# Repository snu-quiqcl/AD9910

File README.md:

# AD9910 Control RTL Code and Python Program
## Overview
## AD9910 Mode

The AD9910 is a Direct Digital Synthesizer (DDS) with four modes of operation: single tone mode, RAM modulation mode, digital ramp modulation mode, and parallel data port modulation mode. In our application, we use only the RAM mode and single tone mode. The source of the three parameters varies in each mode. The sources of these parameters for each mode are listed in the table below.

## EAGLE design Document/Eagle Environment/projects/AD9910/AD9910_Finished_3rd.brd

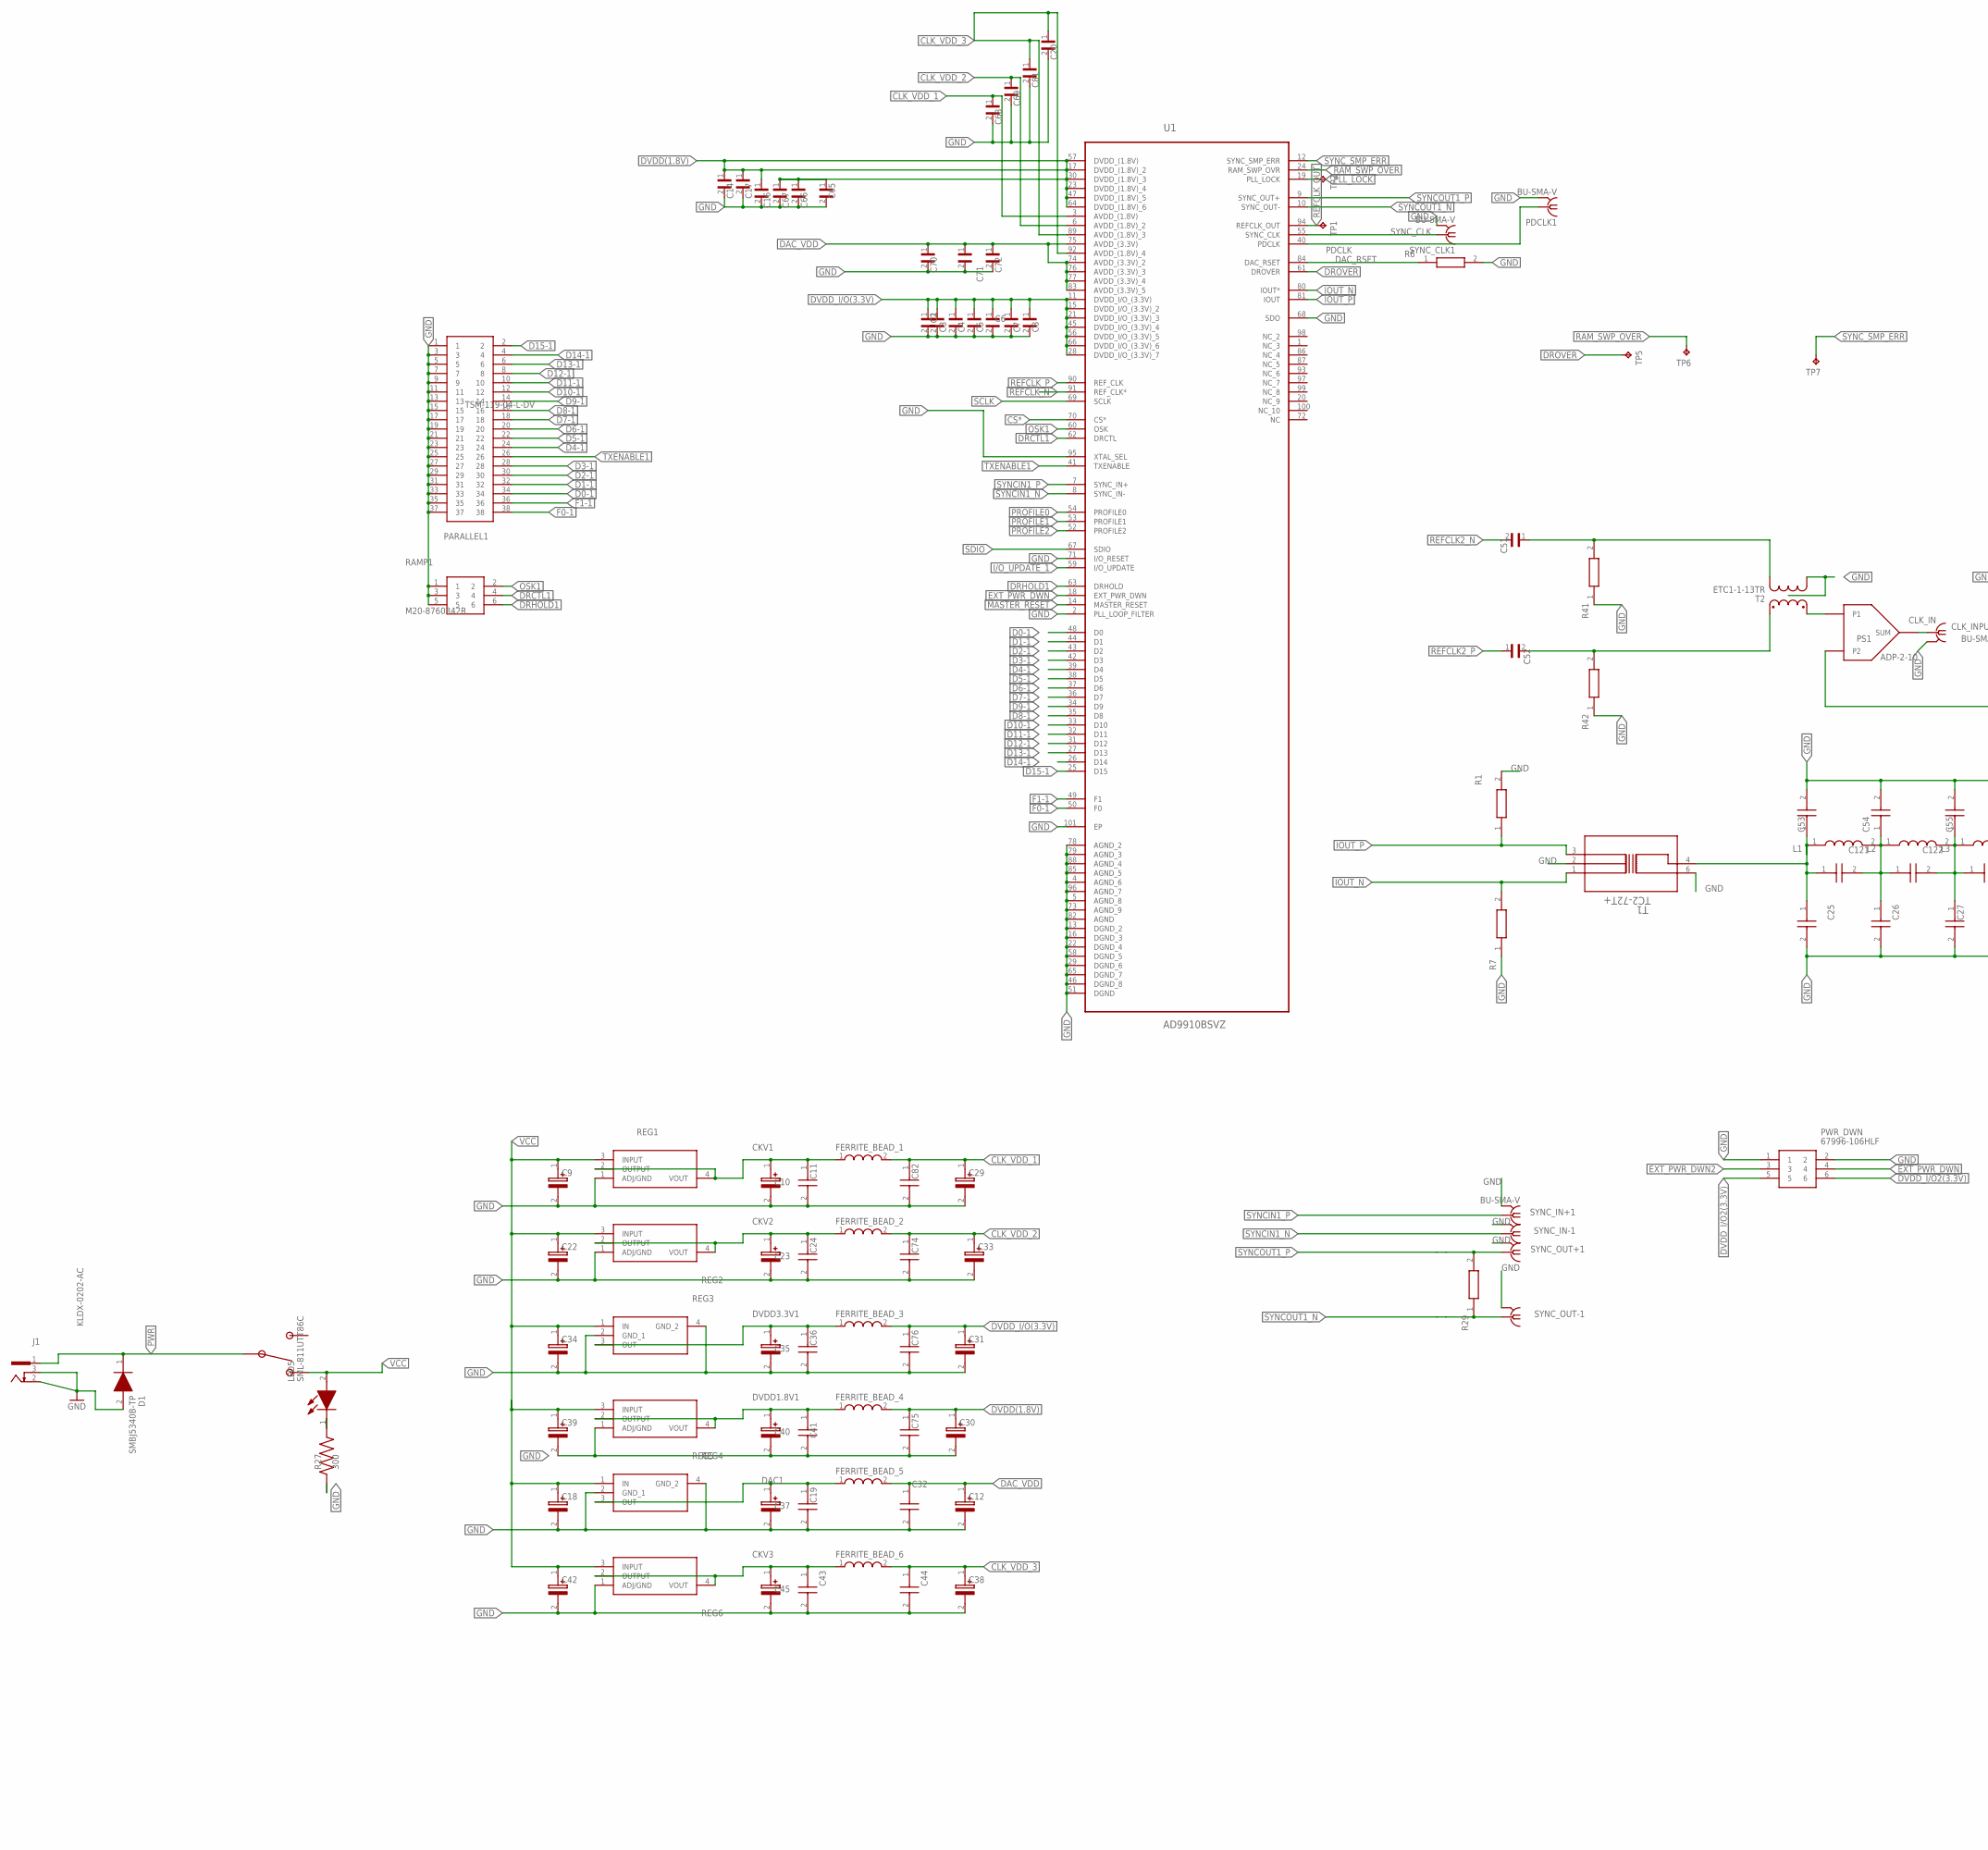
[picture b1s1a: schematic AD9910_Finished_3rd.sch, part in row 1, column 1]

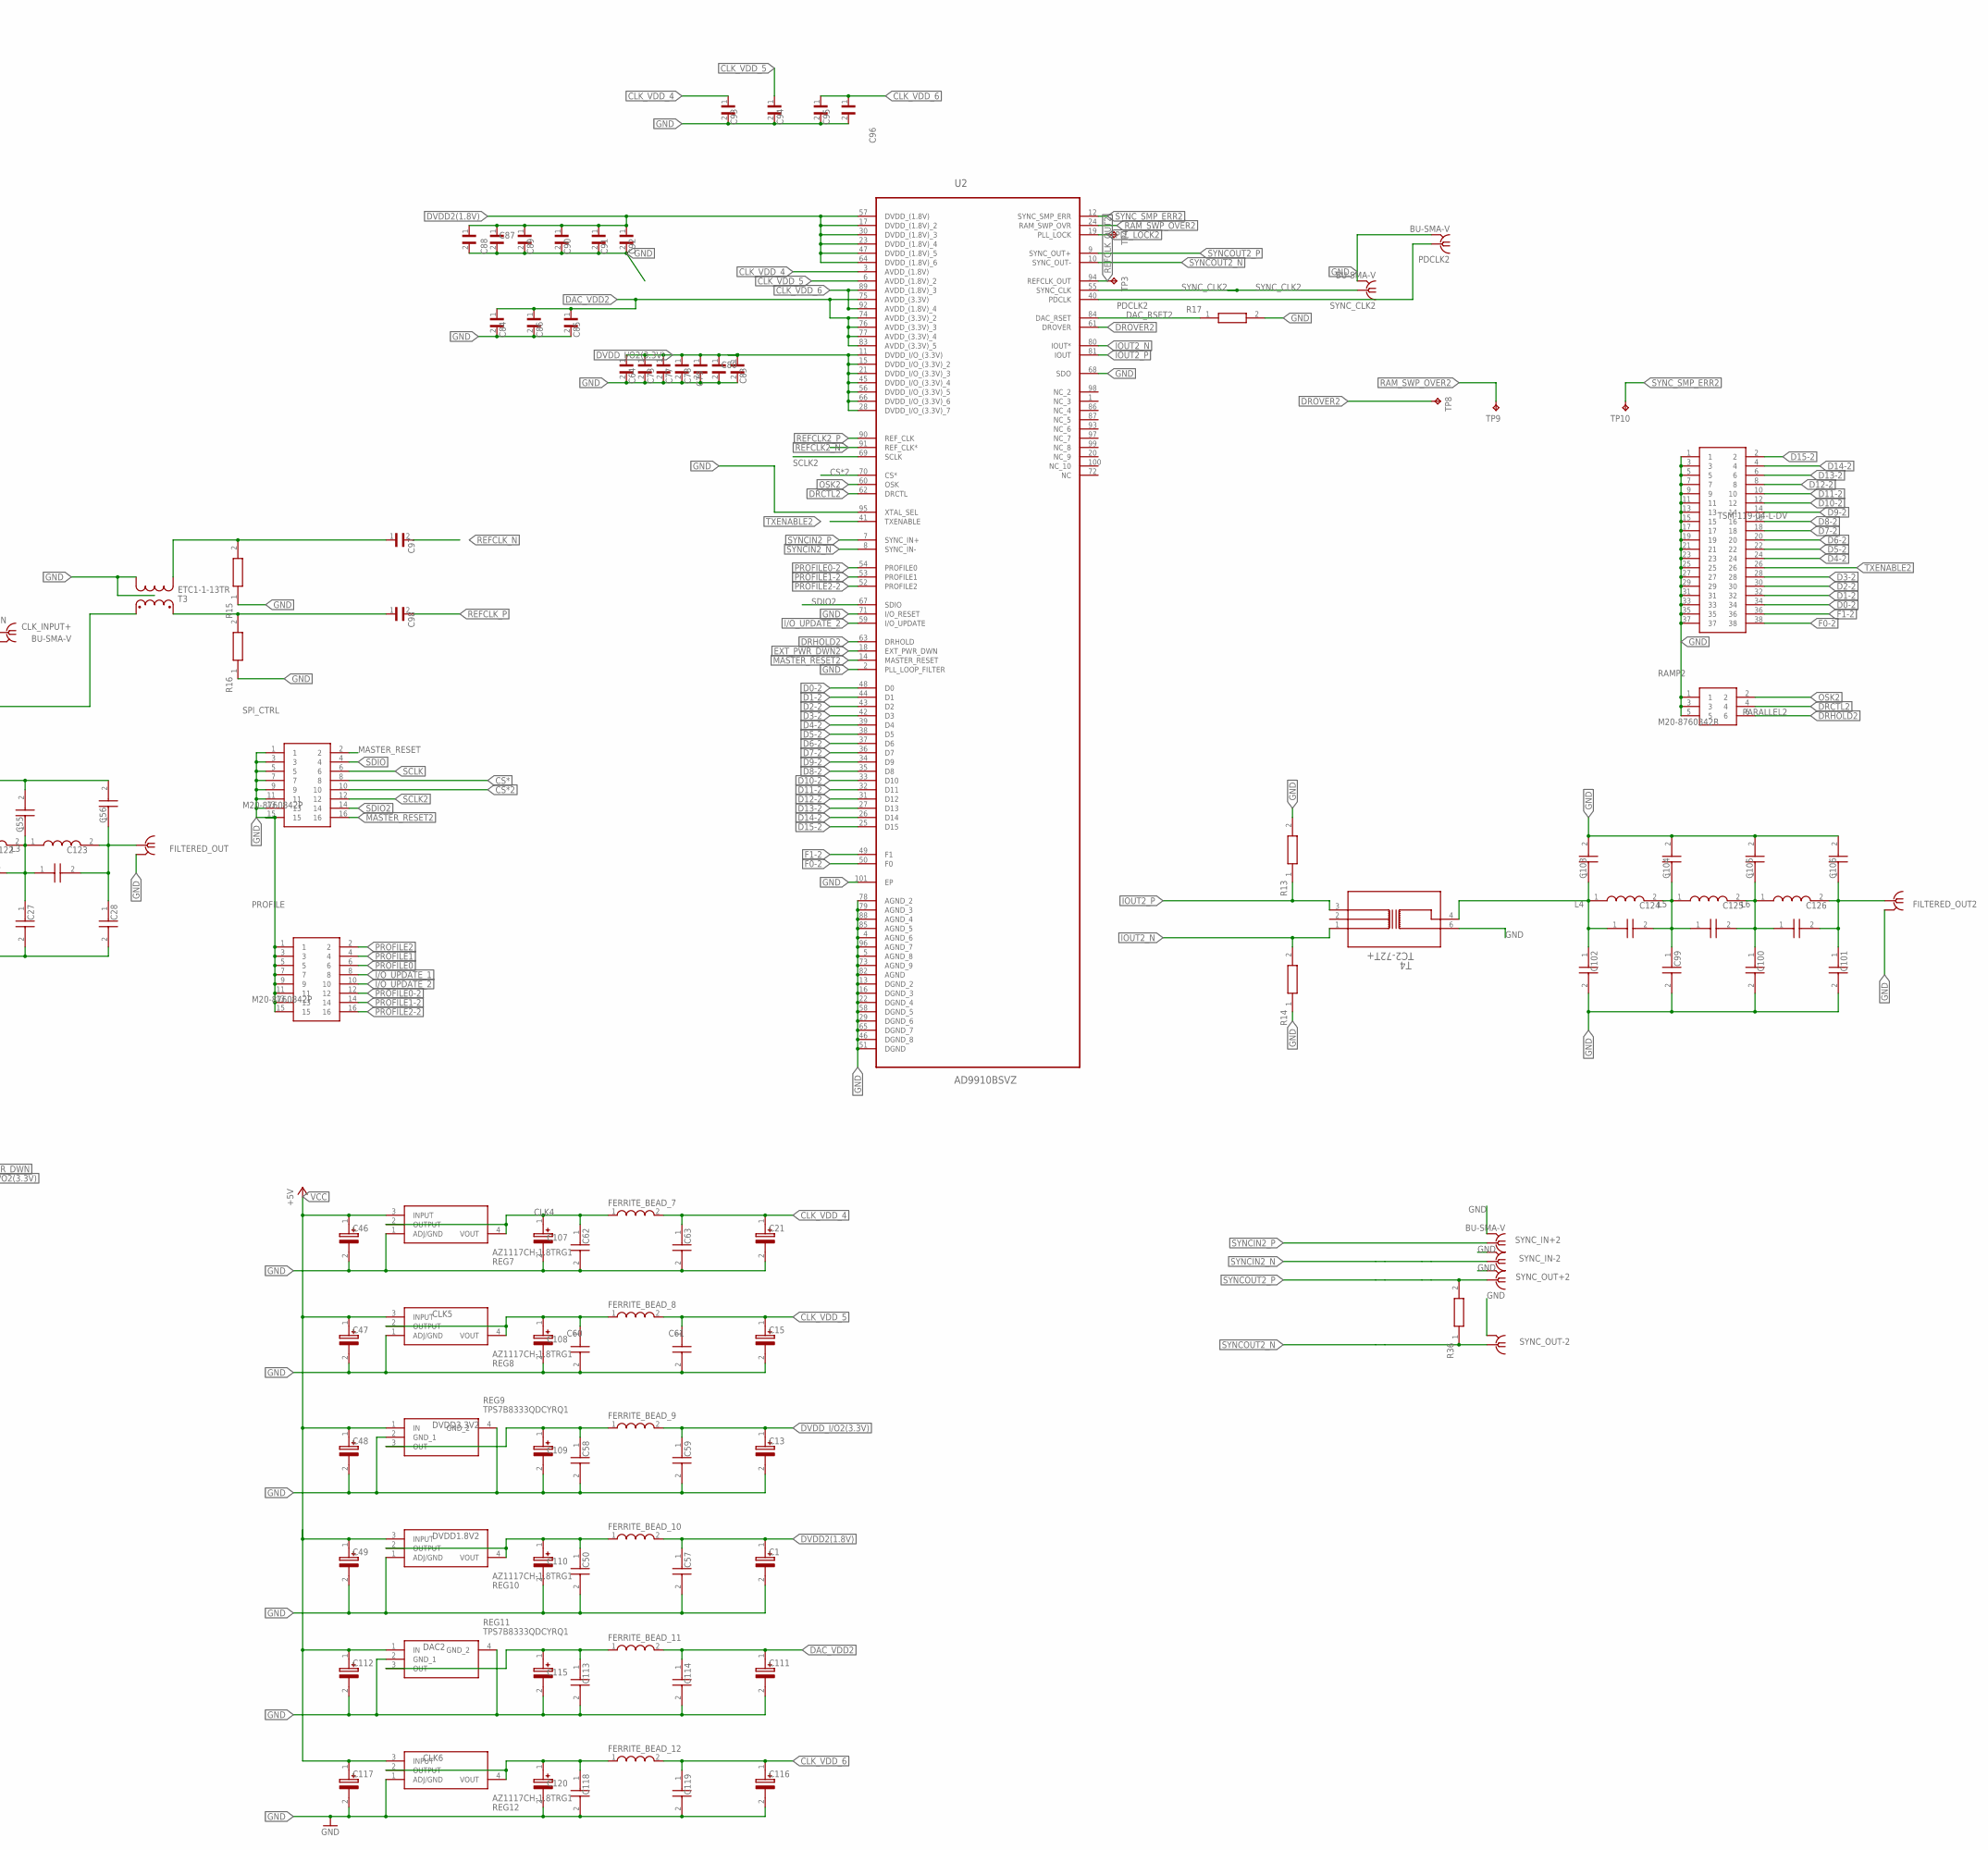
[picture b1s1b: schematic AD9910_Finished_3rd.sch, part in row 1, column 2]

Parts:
C1, C9, C12, C13, C15, C18, C21, C22, C29, C30, C31, C33, C34, C38, C39, C42, C46, C47, C48, C49, C111, C112, C116, C117: T489A106K010ATA2K2; CAPPM3216X180N
C2, C3, C4, C5, C6, C7, C8, C14, C16, C17, C20, C51, C52, C64, C65, C66, C67, C68, C69, C70, C71, C72, C73, C77, C78, C79, C80, C81, C83, C84, C85, C86, C87, C88, C89, C90, C91, C92, C93, C94, C95, C96, C97, C98: GRM022R60G104ME15L; CAPC0402X22N
C10, C23, C35, C37, C40, C45, C107, C108, C109, C110, C115, C120: T491A226K010ATAUTO; CAPPM3216X180N
C11, C19, C24, C32, C36, C41, C43, C44, C74, C75, C76, C82: GRM152D80G105ME15D; CAPC1005X22N
C25, C53, C102, C103, C122, C125: GQM2195C2E2R7CB12D; CAPC2012X100N
C26, C54, C99, C104, C121, C124: GQM2195C2E5R6CB12D; CAPC2012X100N
C27, C55, C100, C105: GQM2195C2E6R8CB12D; CAPC2012X100N
C28, C56, C101, C106: GQM2195C2E3R9BB12D; CAPC2012X100N
C50, C57, C58, C59, C60, C61, C62, C63, C113, C114, C118, C119: GRMMDXR60J105ME05D; CAPC0502X28N
C123, C126: GQM2195C2E1R0BB12D; CAPC2012X100N
CLK_INPUT+: BU-SMA-V
D1: SMBJ5340B-TP; DIOM5336X241N
FERRITE_BEAD_1, FERRITE_BEAD_2, FERRITE_BEAD_3, FERRITE_BEAD_4, FERRITE_BEAD_5, FERRITE_BEAD_6, FERRITE_BEAD_7, FERRITE_BEAD_8, FERRITE_BEAD_9, FERRITE_BEAD_10, FERRITE_BEAD_11, FERRITE_BEAD_12: WE-CBF_0603(WB/HS); WE-CBF_0603(W=2.2)
FILTERED_OUT, FILTERED_OUT2: BU-SMA-H
J1: KLDX-0202-AC; KYCON_KLDX-0202-AC
L1, L4: LQW2BAS18NJ00L; LQW2BAN11NG00L
L2, L5: LQW2BAS22NJ00L; LQW2BAN11NG00L
L3, L6: LQW2BAS27NJ00L; LQW2BAN11NG00L
LED5: SML-811UTT86C; LEDC3412X115N
PARALLEL1, PARALLEL2: TSM-119-04-L-DV; TSM-119-YY-ZZZ-DV
PDCLK1, PDCLK2: BU-SMA-V
PROFILE: M20-8760842P; M208760842P
PS1: ADP-2-10; CD636
PWR_DWN: 67996-106HLF; HDRV6W67P254_2X3_762X483X858P
R1, R7, R13, R14: TNPW020150R0BEED; RESC0603X26N
R6, R17: TNPU040210K0AYEP00; RESC1005X40N
R15, R16, R41, R42: CRCW020124R9FNED; RESC0603X28N
R27: 300; RES_ERA3VEB3000V
R29, R36: CRCW0402100RFKEDC; RESC1005X35N
RAMP1, RAMP2: M20-8760342R; M208760342R
REG1, REG2, REG4, REG6, REG7, REG8, REG10, REG12: AZ1117CH-1.8TRG1; SOT230P700X180-4N
REG3, REG5, REG9, REG11: TPS7B8333QDCYRQ1; SOT230P700X180-4N
SPI_CTRL: M20-8760842P; M208760842P
SW1: 100SP1T2B4M6QE; TOGGLE_RA
SYNC_CLK1, SYNC_CLK2: BU-SMA-V
SYNC_IN+1, SYNC_IN+2: BU-SMA-V
SYNC_IN-1, SYNC_IN-2: BU-SMA-V
SYNC_OUT+1, SYNC_OUT+2: BU-SMA-V
SYNC_OUT-1, SYNC_OUT-2: BU-SMA-V
T1, T4: TC2-72T+; AT1521_MNC
T2, T3: ETC1-1-13TR; SM22
TP1, TP2, TP3, TP4, TP5, TP6, TP7, TP8, TP9, TP10: TPPAD1-13; P1-13
U1, U2: AD9910BSVZ; QFP50P1600X1600X120-101N

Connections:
CKV1: C10.1 (+), C11.1, FERRITE_BEAD_1.1, REG1.2 (OUTPUT), REG1.4 (VOUT)
CKV2: C23.1 (+), C24.1, FERRITE_BEAD_2.1, REG2.2 (OUTPUT), REG2.4 (VOUT)
CKV3: C43.1, C45.1 (+), FERRITE_BEAD_6.1, REG6.2 (OUTPUT), REG6.4 (VOUT)
CLK4: C62.1, C107.1 (+), FERRITE_BEAD_7.1, REG7.2 (OUTPUT), REG7.4 (VOUT)
CLK5: C60.1, C108.1 (+), FERRITE_BEAD_8.1, REG8.2 (OUTPUT), REG8.4 (VOUT)
CLK6: C118.1, C120.1 (+), FERRITE_BEAD_12.1, REG12.2 (OUTPUT), REG12.4 (VOUT)
CLK_IN: CLK_INPUT+.1, PS1.1 (SUM)
CLK_VDD_1: C29.1 (+), C68.1, C82.1, FERRITE_BEAD_1.2, U1.3 (AVDD_(1.8V))
CLK_VDD_2: C33.1 (+), C69.1, C74.1, FERRITE_BEAD_2.2, U1.6 (AVDD_(1.8V)_2)
CLK_VDD_3: C20.1, C38.1 (+), C44.1, C81.1, FERRITE_BEAD_6.2, U1.89 (AVDD_(1.8V)_3), U1.92 (AVDD_(1.8V)_4)
CLK_VDD_4: C21.1 (+), C63.1, C93.1, FERRITE_BEAD_7.2, U2.3 (AVDD_(1.8V))
CLK_VDD_5: C15.1 (+), C61.1, C94.1, FERRITE_BEAD_8.2, U2.6 (AVDD_(1.8V)_2)
CLK_VDD_6: C95.1, C96.1, C116.1 (+), C119.1, FERRITE_BEAD_12.2, U2.89 (AVDD_(1.8V)_3), U2.92 (AVDD_(1.8V)_4)
CS*: SPI_CTRL.8, U1.70 (CS*)
CS*2: SPI_CTRL.10, U2.70 (CS*)
D0-1: PARALLEL1.34, U1.48 (D0)
D0-2: PARALLEL2.34, U2.48 (D0)
D1-1: PARALLEL1.32, U1.44 (D1)
D1-2: PARALLEL2.32, U2.44 (D1)
D2-1: PARALLEL1.30, U1.43 (D2)
D2-2: PARALLEL2.30, U2.43 (D2)
D3-1: PARALLEL1.28, U1.42 (D3)
D3-2: PARALLEL2.28, U2.42 (D3)
D4-1: PARALLEL1.24, U1.39 (D4)
D4-2: PARALLEL2.24, U2.39 (D4)
D5-1: PARALLEL1.22, U1.38 (D5)
D5-2: PARALLEL2.22, U2.38 (D5)
D6-1: PARALLEL1.20, U1.37 (D6)
D6-2: PARALLEL2.20, U2.37 (D6)
D7-1: PARALLEL1.18, U1.36 (D7)
D7-2: PARALLEL2.18, U2.36 (D7)
D8-1: PARALLEL1.16, U1.35 (D8)
D8-2: PARALLEL2.16, U2.35 (D8)
D9-1: PARALLEL1.14, U1.34 (D9)
D9-2: PARALLEL2.14, U2.34 (D9)
D10-1: PARALLEL1.12, U1.33 (D10)
D10-2: PARALLEL2.12, U2.33 (D10)
D11-1: PARALLEL1.10, U1.32 (D11)
D11-2: PARALLEL2.10, U2.32 (D11)
D12-1: PARALLEL1.8, U1.31 (D12)
D12-2: PARALLEL2.8, U2.31 (D12)
D13-1: PARALLEL1.6, U1.27 (D13)
D13-2: PARALLEL2.6, U2.27 (D13)
D14-1: PARALLEL1.4, U1.26 (D14)
D14-2: PARALLEL2.4, U2.26 (D14)
D15-1: PARALLEL1.2, U1.25 (D15)
D15-2: PARALLEL2.2, U2.25 (D15)
DAC1: C19.1, C37.1 (+), FERRITE_BEAD_5.1, REG5.3 (OUT)
DAC2: C113.1, C115.1 (+), FERRITE_BEAD_11.1, REG11.3 (OUT)
DAC_RSET: R6.1, U1.84 (DAC_RSET)
DAC_RSET2: R17.1, U2.84 (DAC_RSET)
DAC_VDD: C12.1 (+), C32.1, C70.1, C71.1, C72.1, FERRITE_BEAD_5.2, U1.74 (AVDD_(3.3V)_2), U1.75 (AVDD_(3.3V)), U1.76 (AVDD_(3.3V)_3), U1.77 (AVDD_(3.3V)_4), U1.83 (AVDD_(3.3V)_5)
DAC_VDD2: C84.1, C85.1, C86.1, C111.1 (+), C114.1, FERRITE_BEAD_11.2, U2.74 (AVDD_(3.3V)_2), U2.75 (AVDD_(3.3V)), U2.76 (AVDD_(3.3V)_3), U2.77 (AVDD_(3.3V)_4), U2.83 (AVDD_(3.3V)_5)
DRCTL1: RAMP1.4, U1.62 (DRCTL)
DRCTL2: RAMP2.4, U2.62 (DRCTL)
DRHOLD1: RAMP1.6, U1.63 (DRHOLD)
DRHOLD2: RAMP2.6, U2.63 (DRHOLD)
DROVER: TP5.TP, U1.61 (DROVER)
DROVER2: TP8.TP, U2.61 (DROVER)
DVDD1.8V1: C40.1 (+), C41.1, FERRITE_BEAD_4.1, REG4.2 (OUTPUT), REG4.4 (VOUT)
DVDD1.8V2: C50.1, C110.1 (+), FERRITE_BEAD_10.1, REG10.2 (OUTPUT), REG10.4 (VOUT)
DVDD2(1.8V): C1.1 (+), C57.1, C87.1, C88.1, C89.1, C90.1, C91.1, C92.1, FERRITE_BEAD_10.2, U2.17 (DVDD_(1.8V)_2), U2.23 (DVDD_(1.8V)_4), U2.30 (DVDD_(1.8V)_3), U2.47 (DVDD_(1.8V)_5), U2.57 (DVDD_(1.8V)), U2.64 (DVDD_(1.8V)_6)
DVDD3.3V1: C35.1 (+), C36.1, FERRITE_BEAD_3.1, REG3.3 (OUT)
DVDD3.3V2: C58.1, C109.1 (+), FERRITE_BEAD_9.1, REG9.3 (OUT)
DVDD(1.8V): C14.1, C16.1, C17.1, C30.1 (+), C65.1, C66.1, C67.1, C75.1, FERRITE_BEAD_4.2, U1.17 (DVDD_(1.8V)_2), U1.23 (DVDD_(1.8V)_4), U1.30 (DVDD_(1.8V)_3), U1.47 (DVDD_(1.8V)_5), U1.57 (DVDD_(1.8V)), U1.64 (DVDD_(1.8V)_6)
DVDD_I/O2(3.3V): C13.1 (+), C59.1, C64.1, C73.1, C77.1, C78.1, C79.1, C80.1, C83.1, FERRITE_BEAD_9.2, PWR_DWN.5, PWR_DWN.6, U2.11 (DVDD_I/O_(3.3V)), U2.15 (DVDD_I/O_(3.3V)_2), U2.21 (DVDD_I/O_(3.3V)_3), U2.28 (DVDD_I/O_(3.3V)_7), U2.45 (DVDD_I/O_(3.3V)_4), U2.56 (DVDD_I/O_(3.3V)_5), U2.66 (DVDD_I/O_(3.3V)_6)
DVDD_I/O(3.3V): C2.1, C3.1, C4.1, C5.1, C6.1, C7.1, C8.1, C31.1 (+), C76.1, FERRITE_BEAD_3.2, U1.11 (DVDD_I/O_(3.3V)), U1.15 (DVDD_I/O_(3.3V)_2), U1.21 (DVDD_I/O_(3.3V)_3), U1.28 (DVDD_I/O_(3.3V)_7), U1.45 (DVDD_I/O_(3.3V)_4), U1.56 (DVDD_I/O_(3.3V)_5), U1.66 (DVDD_I/O_(3.3V)_6)
EXT_PWR_DWN: PWR_DWN.4, U1.18 (EXT_PWR_DWN)
EXT_PWR_DWN2: PWR_DWN.3, U2.18 (EXT_PWR_DWN)
F0-1: PARALLEL1.38, U1.50 (F0)
F0-2: PARALLEL2.38, U2.50 (F0)
F1-1: PARALLEL1.36, U1.49 (F1)
F1-2: PARALLEL2.36, U2.49 (F1)
GND: C1.2 (-), C2.2, C3.2, C4.2, C5.2, C6.2, C7.2, C8.2, C9.2 (-), C10.2 (-), C11.2, C12.2 (-), C13.2 (-), C14.2, C15.2 (-), C16.2, C17.2, C18.2 (-), C19.2, C20.2, C21.2 (-), C22.2 (-), C23.2 (-), C24.2, C25.2, C26.2, C27.2, C28.2, C29.2 (-), C30.2 (-), C31.2 (-), C32.2, C33.2 (-), C34.2 (-), C35.2 (-), C36.2, C37.2 (-), C38.2 (-), C39.2 (-), C40.2 (-), C41.2, C42.2 (-), C43.2, C44.2, C45.2 (-), C46.2 (-), C47.2 (-), C48.2 (-), C49.2 (-), C50.2, C53.2, C54.2, C55.2, C56.2, C57.2, C58.2, C59.2, C60.2, C61.2, C62.2, C63.2, C64.2, C65.2, C66.2, C67.2, C68.2, C69.2, C70.2, C71.2, C72.2, C73.2, C74.2, C75.2, C76.2, C77.2, C78.2, C79.2, C80.2, C81.2, C82.2, C83.2, C84.2, C85.2, C86.2, C87.2, C88.2, C89.2, C90.2, C91.2, C92.2, C93.2, C94.2, C95.2, C96.2, C99.2, C100.2, C101.2, C102.2, C103.2, C104.2, C105.2, C106.2, C107.2 (-), C108.2 (-), C109.2 (-), C110.2 (-), C111.2 (-), C112.2 (-), C113.2, C114.2, C115.2 (-), C116.2 (-), C117.2 (-), C118.2, C119.2, C120.2 (-), CLK_INPUT+.2, CLK_INPUT+.3 (2), CLK_INPUT+.4 (2), CLK_INPUT+.5 (2), D1.2 (A), FILTERED_OUT.2, FILTERED_OUT.3 (2), FILTERED_OUT.4 (2), FILTERED_OUT.5 (2), FILTERED_OUT2.2, FILTERED_OUT2.3 (2), FILTERED_OUT2.4 (2), FILTERED_OUT2.5 (2), J1.2, J1.3, PARALLEL1.1, PARALLEL1.3, PARALLEL1.5, PARALLEL1.7, PARALLEL1.9, PARALLEL1.11, PARALLEL1.13, PARALLEL1.15, PARALLEL1.17, PARALLEL1.19, PARALLEL1.21, PARALLEL1.23, PARALLEL1.25, PARALLEL1.27, PARALLEL1.29, PARALLEL1.31, PARALLEL1.33, PARALLEL1.35, PARALLEL1.37, PARALLEL2.1, PARALLEL2.3, PARALLEL2.5, PARALLEL2.7, PARALLEL2.9, PARALLEL2.11, PARALLEL2.13, PARALLEL2.15, PARALLEL2.17, PARALLEL2.19, PARALLEL2.21, PARALLEL2.23, PARALLEL2.25, PARALLEL2.27, PARALLEL2.29, PARALLEL2.31, PARALLEL2.33, PARALLEL2.35, PARALLEL2.37, PDCLK1.2, PDCLK1.3 (2), PDCLK1.4 (2), PDCLK1.5 (2), PDCLK2.2, PDCLK2.3 (2), PDCLK2.4 (2), PDCLK2.5 (2), PROFILE.1, PROFILE.3, PROFILE.5, PROFILE.7, PROFILE.9, PROFILE.11, PROFILE.13, PROFILE.15, PS1.2 (GND), PS1.5 (GND), PS1.6 (GND), PWR_DWN.1, PWR_DWN.2, R1.2, R6.2, R7.1, R13.2, R14.1, R15.1, R16.1, R17.2, R27.1, R41.1, R42.1, RAMP1.1, RAMP1.3, RAMP1.5, RAMP2.1, RAMP2.3, RAMP2.5, REG1.1 (ADJ/GND), REG2.1 (ADJ/GND), REG3.2 (GND_1), REG3.4 (GND_2), REG4.1 (ADJ/GND), REG5.2 (GND_1), REG5.4 (GND_2), REG6.1 (ADJ/GND), REG7.1 (ADJ/GND), REG8.1 (ADJ/GND), REG9.2 (GND_1), REG9.4 (GND_2), REG10.1 (ADJ/GND), REG11.2 (GND_1), REG11.4 (GND_2), REG12.1 (ADJ/GND), SPI_CTRL.1, SPI_CTRL.3, SPI_CTRL.5, SPI_CTRL.7, SPI_CTRL.9, SPI_CTRL.11, SPI_CTRL.13, SPI_CTRL.15, SYNC_CLK1.2, SYNC_CLK1.3 (2), SYNC_CLK1.4 (2), SYNC_CLK1.5 (2), SYNC_CLK2.2, SYNC_CLK2.3 (2), SYNC_CLK2.4 (2), SYNC_CLK2.5 (2), SYNC_IN+1.2, SYNC_IN+1.3 (2), SYNC_IN+1.4 (2), SYNC_IN+1.5 (2), SYNC_IN+2.2, SYNC_IN+2.3 (2), SYNC_IN+2.4 (2), SYNC_IN+2.5 (2), SYNC_IN-1.2, SYNC_IN-1.3 (2), SYNC_IN-1.4 (2), SYNC_IN-1.5 (2), SYNC_IN-2.2, SYNC_IN-2.3 (2), SYNC_IN-2.4 (2), SYNC_IN-2.5 (2), SYNC_OUT+1.2, SYNC_OUT+1.3 (2), SYNC_OUT+1.4 (2), SYNC_OUT+1.5 (2), SYNC_OUT+2.2, SYNC_OUT+2.3 (2), SYNC_OUT+2.4 (2), SYNC_OUT+2.5 (2), SYNC_OUT-1.2, SYNC_OUT-1.3 (2), SYNC_OUT-1.4 (2), SYNC_OUT-1.5 (2), SYNC_OUT-2.2, SYNC_OUT-2.3 (2), SYNC_OUT-2.4 (2), SYNC_OUT-2.5 (2), T1.2, T1.6, T2.2, T2.4, T3.2, T3.4, T4.6, U1.2 (PLL_LOOP_FILTER), U1.4 (AGND_6), U1.5 (AGND_8), U1.13 (DGND_2), U1.16 (DGND_3), U1.22 (DGND_4), U1.29 (DGND_6), U1.46 (DGND_8), U1.51 (DGND), U1.58 (DGND_5), U1.65 (DGND_7), U1.68 (SDO), U1.71 (I/O_RESET), U1.73 (AGND_9), U1.78 (AGND_2), U1.79 (AGND_3), U1.82 (AGND), U1.85 (AGND_5), U1.88 (AGND_4), U1.95 (XTAL_SEL), U1.96 (AGND_7), U1.101 (EP), U2.2 (PLL_LOOP_FILTER), U2.4 (AGND_6), U2.5 (AGND_8), U2.13 (DGND_2), U2.16 (DGND_3), U2.22 (DGND_4), U2.29 (DGND_6), U2.46 (DGND_8), U2.51 (DGND), U2.58 (DGND_5), U2.65 (DGND_7), U2.68 (SDO), U2.71 (I/O_RESET), U2.73 (AGND_9), U2.78 (AGND_2), U2.79 (AGND_3), U2.82 (AGND), U2.85 (AGND_5), U2.88 (AGND_4), U2.95 (XTAL_SEL), U2.96 (AGND_7), U2.101 (EP)
I/O_UPDATE_1: PROFILE.8, U1.59 (I/O_UPDATE)
I/O_UPDATE_2: PROFILE.10, U2.59 (I/O_UPDATE)
IOUT2_N: R14.2, T4.1, U2.80 (IOUT*)
IOUT2_P: R13.1, T4.3, U2.81 (IOUT)
IOUT_N: R7.2, T1.1, U1.80 (IOUT*)
IOUT_P: R1.1, T1.3, U1.81 (IOUT)
MASTER_RESET: SPI_CTRL.2, U1.14 (MASTER_RESET)
MASTER_RESET2: SPI_CTRL.16, U2.14 (MASTER_RESET)
N5: C51.1, R41.2, T2.3
unnamed: PS1.3 (P1), T2.5
unnamed: PS1.4 (P2), T3.5
unnamed: C102.1, C103.1, C124.1, L4.1, T4.4
unnamed: C99.1, C104.1, C124.2, C125.1, L4.2, L5.1
unnamed: C100.1, C105.1, C125.2, C126.1, L5.2, L6.1
unnamed: C101.1, C106.1, C126.2, FILTERED_OUT2.1, L6.2
unnamed: C98.1, R16.2, T3.1
unnamed: C97.1, R15.2, T3.3
unnamed: LED5.1 (K), R27.2
unnamed: C52.2, R42.2, T2.1
unnamed: C25.1, C53.1, C121.1, L1.1, T1.4
unnamed: C26.1, C54.1, C121.2, C122.1, L1.2, L2.1
unnamed: C27.1, C55.1, C122.2, C123.1, L2.2, L3.1
unnamed: C28.1, C56.1, C123.2, FILTERED_OUT.1, L3.2
OSK1: RAMP1.2, U1.60 (OSK)
OSK2: RAMP2.2, U2.60 (OSK)
PDCLK: PDCLK1.1, U1.40 (PDCLK)
PDCLK2: PDCLK2.1, U2.40 (PDCLK)
PLL_LOCK: TP2.TP, U1.19 (PLL_LOCK)
PLL_LOCK2: TP4.TP, U2.19 (PLL_LOCK)
PROFILE0: PROFILE.6, U1.54 (PROFILE0)
PROFILE0-2: PROFILE.12, U2.54 (PROFILE0)
PROFILE1: PROFILE.4, U1.53 (PROFILE1)
PROFILE1-2: PROFILE.14, U2.53 (PROFILE1)
PROFILE2: PROFILE.2, U1.52 (PROFILE2)
PROFILE2-2: PROFILE.16, U2.52 (PROFILE2)
PWR: D1.1 (K), J1.1, SW1.2 (COM)
RAM_SWP_OVER: TP6.TP, U1.24 (RAM_SWP_OVR)
RAM_SWP_OVER2: TP9.TP, U2.24 (RAM_SWP_OVR)
REFCLK2_N: C51.2, U2.91 (REF_CLK*)
REFCLK2_P: C52.1, U2.90 (REF_CLK)
REFCLK_N: C97.2, U1.91 (REF_CLK*)
REFCLK_OUT: TP1.TP, U1.94 (REFCLK_OUT)
REFCLK_OUT2: TP3.TP, U2.94 (REFCLK_OUT)
REFCLK_P: C98.2, U1.90 (REF_CLK)
SCLK: SPI_CTRL.6, U1.69 (SCLK)
SCLK2: SPI_CTRL.12, U2.69 (SCLK)
SDIO: SPI_CTRL.4, U1.67 (SDIO)
SDIO2: SPI_CTRL.14, U2.67 (SDIO)
SYNCIN1_N: SYNC_IN-1.1, U1.8 (SYNC_IN-)
SYNCIN1_P: SYNC_IN+1.1, U1.7 (SYNC_IN+)
SYNCIN2_N: SYNC_IN-2.1, U2.8 (SYNC_IN-)
SYNCIN2_P: SYNC_IN+2.1, U2.7 (SYNC_IN+)
SYNCOUT1_N: R29.1, SYNC_OUT-1.1, U1.10 (SYNC_OUT-)
SYNCOUT1_P: R29.2, SYNC_OUT+1.1, U1.9 (SYNC_OUT+)
SYNCOUT2_N: R36.1, SYNC_OUT-2.1, U2.10 (SYNC_OUT-)
SYNCOUT2_P: R36.2, SYNC_OUT+2.1, U2.9 (SYNC_OUT+)
SYNC_CLK: SYNC_CLK1.1, U1.55 (SYNC_CLK)
SYNC_CLK2: SYNC_CLK2.1, U2.55 (SYNC_CLK)
SYNC_SMP_ERR: TP7.TP, U1.12 (SYNC_SMP_ERR)
SYNC_SMP_ERR2: TP10.TP, U2.12 (SYNC_SMP_ERR)
TXENABLE1: PARALLEL1.26, U1.41 (TXENABLE)
TXENABLE2: PARALLEL2.26, U2.41 (TXENABLE)
VCC: C9.1 (+), C18.1 (+), C22.1 (+), C34.1 (+), C39.1 (+), C42.1 (+), C46.1 (+), C47.1 (+), C48.1 (+), C49.1 (+), C112.1 (+), C117.1 (+), LED5.2 (A), REG1.3 (INPUT), REG2.3 (INPUT), REG3.1 (IN), REG4.3 (INPUT), REG5.1 (IN), REG6.3 (INPUT), REG7.3 (INPUT), REG8.3 (INPUT), REG9.1 (IN), REG10.3 (INPUT), REG11.1 (IN), REG12.3 (INPUT), SW1.3

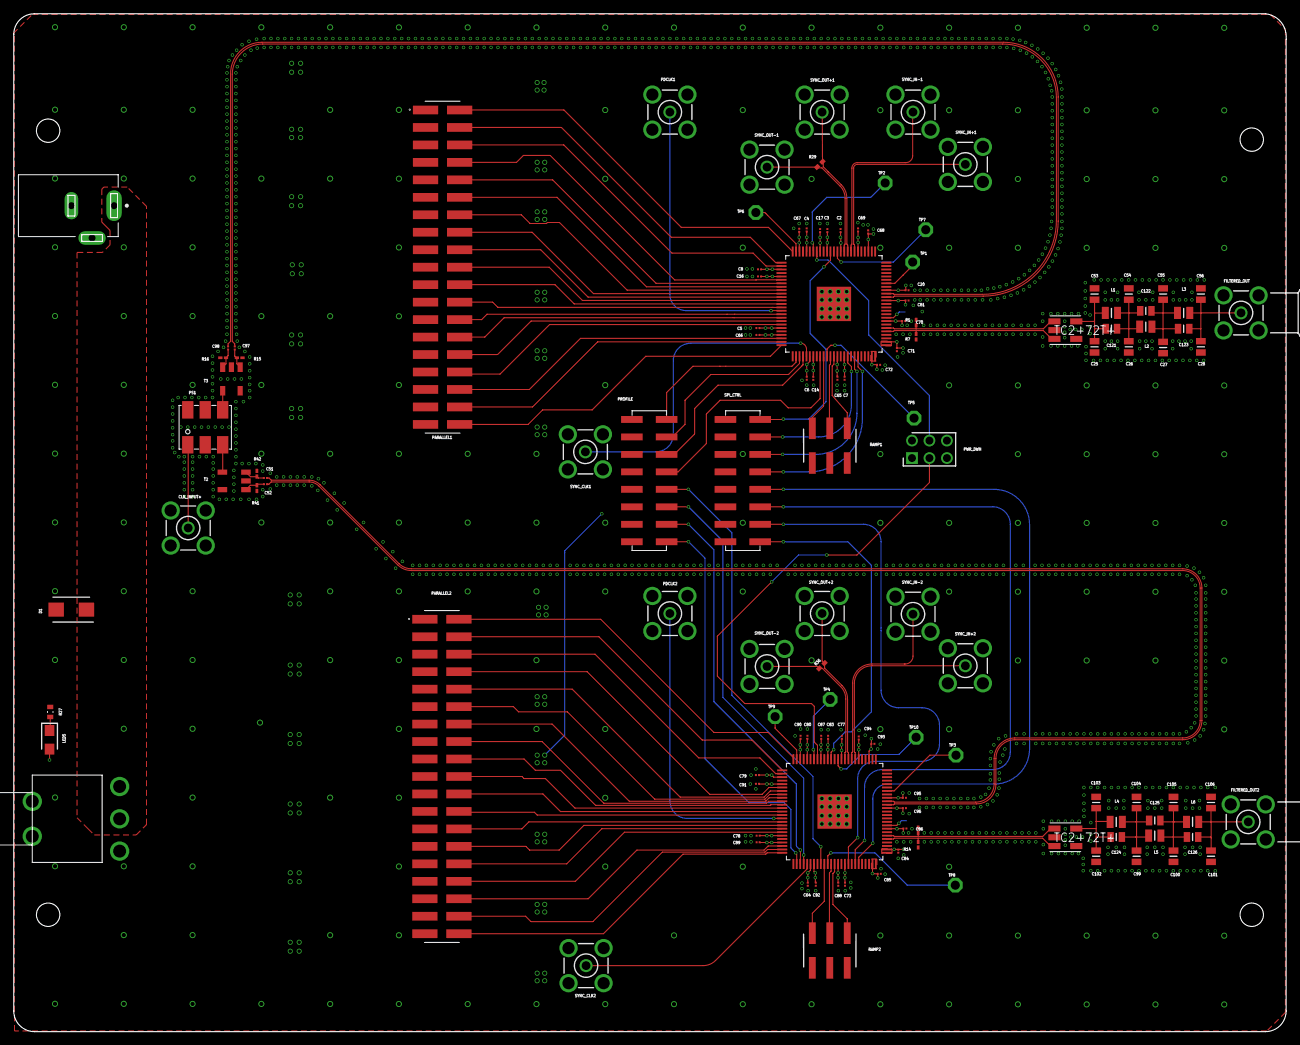
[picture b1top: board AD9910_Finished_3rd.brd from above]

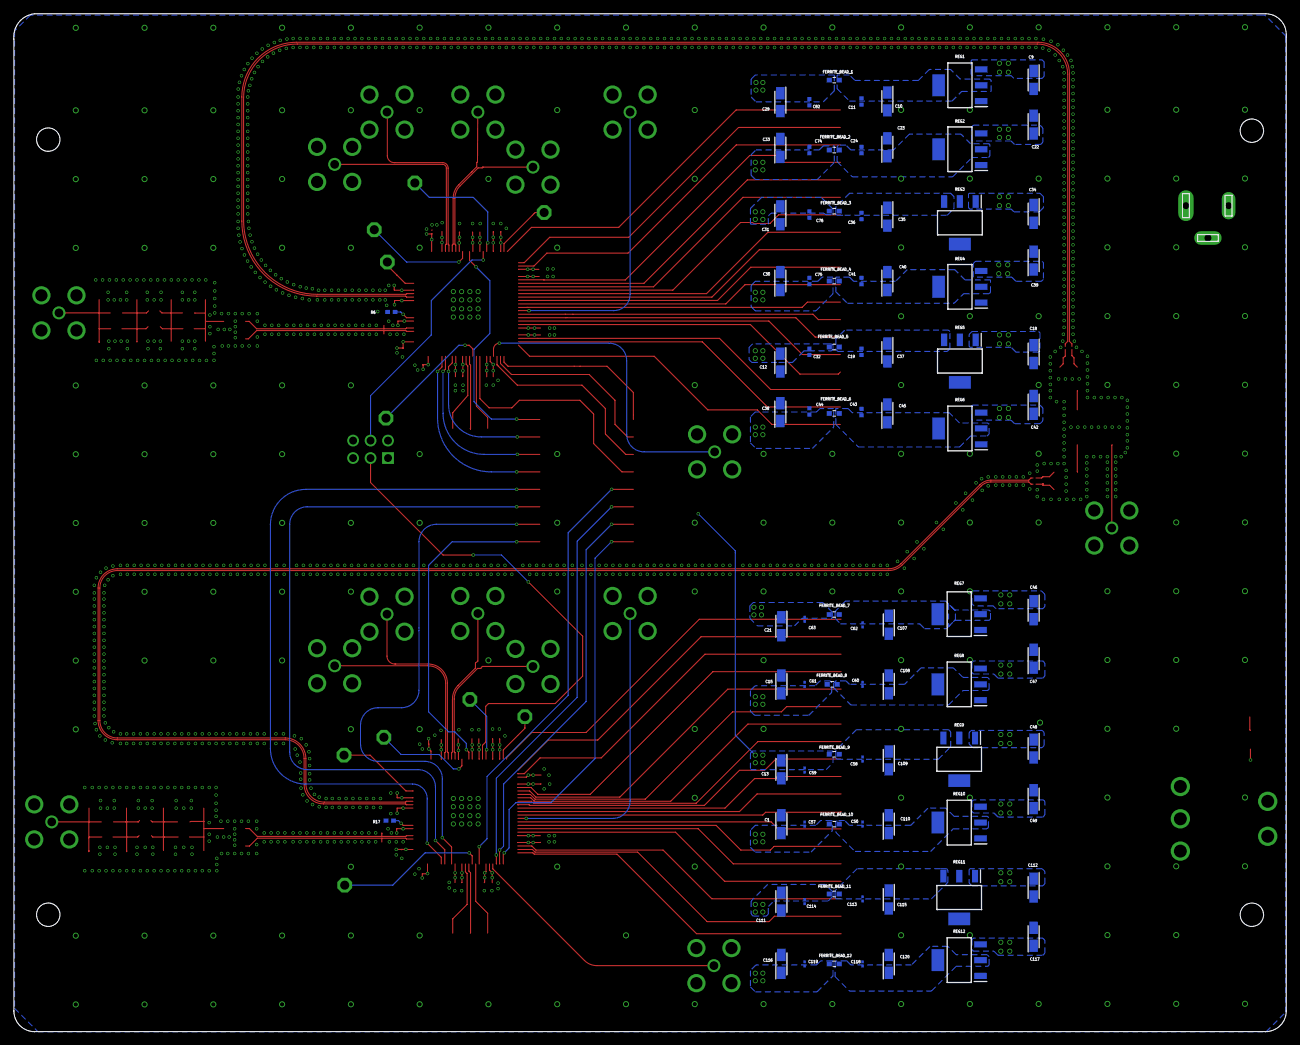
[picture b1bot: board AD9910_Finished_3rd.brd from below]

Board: 4 copper layers, 185.0 x 148.0 mm, 212 parts (86 on the bottom side), 137 nets.

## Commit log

2020-08-05 AD9912 ArtyS7 AD9912(not wirtten) codes were added
2020-08-06 temporary python file and block diagram(PPT file) is added
2020-08-06 PPT for 360 line finished
2020-08-06 other things
2020-08-07 singletone profile, ASF, POW, FTW write, write16, 32, 64 code was written
2020-08-07 AD9912 verilog code was modified for AD9910 code
2020-08-07 AD9912 testbench code was added
2020-08-07 main.sv was completed
2020-08-07 example code was added
2020-08-09 verilog code from vivado17.4 version was added
2020-08-09 code was revised
2020-08-09 Debug mode was added & zeros were added to write32 and write16
2020-08-09 big file (wdb) deleted and ioupdate FSM in main.sv was corrected to not to initiate WRT, \r\n in receiver.sv was corrected int value and simulation was completed
2020-08-09 Licnese
2020-08-10 Arduino simple test code was written (test was completed)
2020-08-10 AD9910 test code was written
2020-08-10 Rx code was resolved
2020-08-10 Tx code Rx code resolved(Rx IO update part should be deleted when we check other part)
2020-08-10 Todo list added
2020-08-10 binary output in TEST added
2020-08-11 parallel output and other functionality implementation start
2020-08-11 AD9910 module development start
2020-08-11 module ppt was updated
2020-08-11 Code was updated
2020-08-12 dds_parallel_write was written but it needs revision
2020-08-12 AD9910 module revision of block diagram(not complete)
2020-08-12 AD9910 module revising
2020-08-12 writing AD9910 code
2020-08-13 spi module is being made and ARTIQ spi module is being researched
2020-08-13 Verilog code was recovered
2020-08-13 AD9910 will be recovered
2020-08-13 Verilog code was recovered since design was changed. After design is fully made, let's make code
2020-08-13 Artiq SPI module Updated
2020-08-16 AD9910 spi module is considered and gto_core changed work compatiably with new sequencer
2020-08-16 Report of AD9910 test was written simply(photo should be added)
2020-08-17 AD9910 spi module was updated & spi module is being writen
2020-08-18 SPI module was made(simple test was finished)
2020-08-18 spi off pin was removed and cs inst was reduced to 8
2020-08-18 spi module including IOBUF was made and tested simply
2020-08-18 selected en was changed to register
2020-08-18 gpo_core is written. Test is needed
2020-08-19 gpo_core is made and simply tested
2020-08-19 rto_core code is written and need to be seen one more time
2020-08-19 rto_core module is modified
2020-08-19 dummy files were deleted
2020-08-19 AD9910 gpi_core, rti_core are considered and gpo_core, rto_core was changed to using addr
2020-08-19 gpo_core using addr was resolved
2020-08-19 gpo_core_prime does not use addr
2020-08-20 Todo added(profile and profile control) and timestamp error logic is resolved
2020-08-20 ad9910 driver is made and simply being tested
2020-08-20 parallel, profile, io update port was added
2020-08-20 reset input is added
2020-08-21 AD9910 function is considered
2020-08-21 FSM is modified and implement is finished. simulation should be conducted and ja_1 should be considered
2020-08-23 ad9910 file is being considered
2020-08-23 parallel code is written
2020-08-23 ck_io pins and DAC module was deleted (ck_io is equal to jd pins) and IOBUF was made for each CS pins
2020-08-23 function to add was simply wrietten in comment
2020-08-24 uart convertor added and read function is added
2020-08-24 verilog code convertor added
2020-08-24 make list was corrected considering little endian
2020-08-25 new design is added
2020-08-25 fifo write and set count was added
2020-08-25 Test is being implemented
2020-08-26 new test is done. delay_cycle function should be considered
2020-08-26 ram code and exception read code was added
2020-08-26 READ EXCEPTION was added to FSM
2020-08-26 error was corrected in exp5
2020-08-26 exp5 test was finished. Serial receive should be tested
2020-08-27 exp5 code was corrected
2020-08-27 Verilog simulation is being implemented
2020-08-27 Report was updated
2020-08-27 write function error was corrected
2020-08-27 Some other test is implemented
2020-08-27 presentation
2020-08-31 Previous code and experiment was finished
2020-08-31 full simulation file maker written
2020-08-31 new presentation
2020-08-31 New experiment
2020-09-01 No change
2020-09-01 presentation update
2023-01-17 New AD9910V2_0 branch added
2023-01-17 Documents added
2023-01-17 manual code added & write32 duration changed
2023-01-31 Debugging ppt was separated, and documents was added
2023-02-03 RAM code updated and tested
2023-02-03 Final report is added
2023-02-06 AD9910 board report added
2023-06-16 IBIS model added
2023-11-09 deleted meaningless files
2023-11-10 TEST -> 0
2023-11-10 FM modulation code added
2023-11-11 FM modulation code update
2023-11-12 Simulation works well
2023-11-13 Frequency Modulation done
2023-11-27 Noise analysis
2023-12-01 Trigger Function is on the Debugging
2023-12-04 shift bug fixed
2023-12-04 clear
2023-12-04 simulation done
2023-12-05 Trigger stop makes driver reset
2023-12-05 bit write done
2023-12-06 mcs filed created
2024-03-15 Only necessary files are left
2024-03-21 AD9910 Simplification is on the work
2024-04-12 Simplification from bulky files
    Create vivado project with vivado_prj_manager
2024-04-12 Python Code update
2024-04-15 GTH clock ports are fixed
2024-04-15 IOBUF -> only one IOBUF is remained
    Input function is diabled temporary since it cause error now....
2024-04-17 TEST done. mcs files added
2024-04-24 Top module option added
2024-06-04 Direct mux -> register
2024-06-04 Unecessary method are removed
2024-06-05 Flash file is replaced
2024-06-05 Code revision
2024-06-05 xdc file revision
2024-06-05 code revision and BUFG added to resolve high FANOUT of reset

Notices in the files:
parts and their libraries:
Wurth_Elektronik_Passive_rev15d: Copyright: Würth Elektronik
COPYRIGHT: Copyright (C) 2022 Ultra Librarian. All rights reserved.
